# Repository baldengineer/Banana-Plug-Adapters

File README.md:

to USB-A")

These adpaters let you plug common power types into a bench power supply. They require a little bit of caution on your side. For example, don't apply 9 volts to the USB adapter!

Each adapter is two pieces made from a single PCB. The part that holds the banana plugs inserts into the adapter part. Then you solder them together. 

## To use them.
* One pack of [Ponoma 72918 4mm banana plug](https://octopart.com/72918-pomona+electronics-585505?r=sp). 
* Break off the two M3 holes
* Use the tabs to solder them together at 90 degrees
* Optional, add LED with current limiting resistor. 
* Optional, clamping diode.
* Plug into power supply. :)

## Discuss on Discord
Join the [AddOhms/Baldengineer Discord](https://discord.gg/Q3xzyuWqm6) to discuss this project.

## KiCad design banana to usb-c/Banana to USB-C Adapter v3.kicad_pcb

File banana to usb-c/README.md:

# Banana Plug to USB-C (Power Only) Adapter

Based on the `USB4125-GF-A` 6 position surface mount connector.

## Version 3: DFP Fix
Version 2 had placements for pull-down resistors. As the DFP, this board should have pull-up resistors. Turns out, most UFP devices don't care so v2 works fine in most cases.

### Status
2024-OCT-20: V3 has not been tested yet.

## DFP Pull-Up Values
| **DFP Advertisement** | **R Pull-Up to 4.75 - 5.5 V** | **R Pull-Up to 3.3 ±5%** |
| :--- | :---: | :---: |
| **Default USB PWR** | 56 kΩ ± 20% | 36 kΩ ± 20% |
| **1.5 A at 5 V** | 22 kΩ ± 5%  | 12 kΩ ± 5% |
| **3.0 A at 5V** | 10 kΩ ± 5% | 4.7 kΩ ± 5% |

[Values from Infineon KB Article](https://community.infineon.com/t5/Knowledge-Base-Articles/USB-Type-C-connector-Rp-Rd-and-Ra-termination-resistors/ta-p/253544)

## Discuss on Discord
Join the [AddOhms/Baldengineer Discord](https://discord.gg/Q3xzyuWqm6) to discuss this project

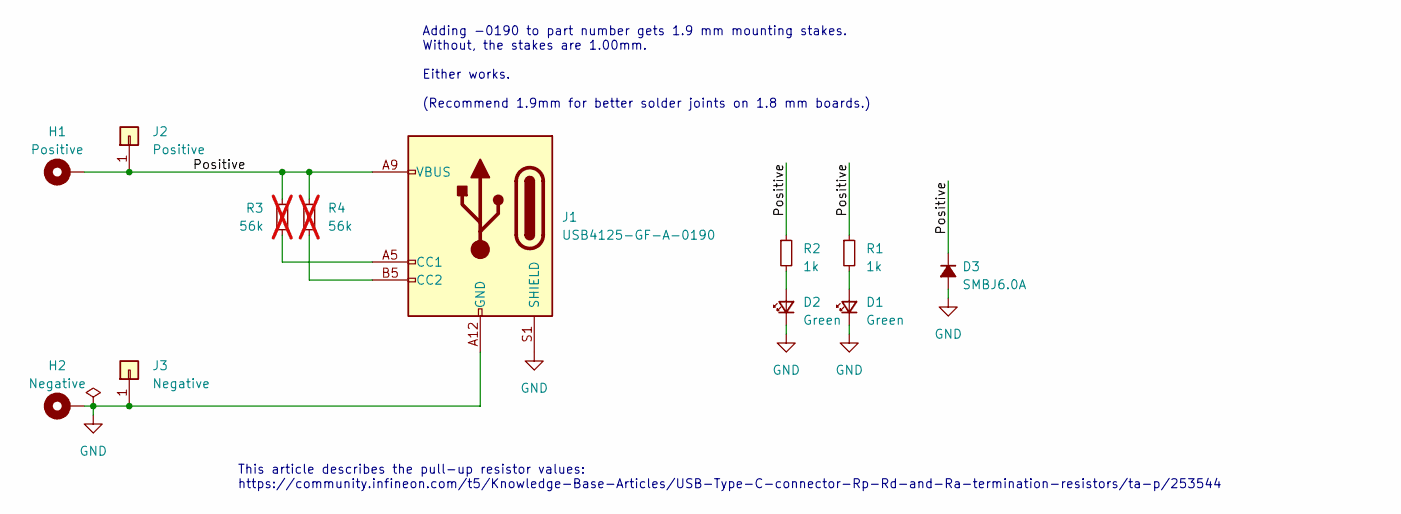
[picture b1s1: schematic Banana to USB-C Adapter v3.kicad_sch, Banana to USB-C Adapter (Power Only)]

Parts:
D1, D2: Green; LED_1206_3216Metric_Pad1.42x1.75mm_HandSolder
D3: SMBJ6.0A; D_SMA-SMB_Universal_Handsoldering
H1: Positive; MountingHole_3.2mm_M3_Pad_Via
H2: Negative; MountingHole_3.2mm_M3_Pad_Via
J1: USB4125-GF-A-0190; USB_C_Receptacle_GCT_USB4125-xx-x_6P_TopMnt_Horizontal
J2: Positive; PinHeader_1x01_P2.54mm_Vertical
J3: Negative; PinHeader_1x01_P2.54mm_Vertical
R1, R2: 1k; R_1206_3216Metric_Pad1.30x1.75mm_HandSolder
R3, R4: 56k; R_1206_3216Metric_Pad1.30x1.75mm_HandSolder; not fitted

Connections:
/Positive: D3.1 (K), H1.1, J1.A9 (VBUS), J1.B9 (VBUS), J2.1, R1.1, R2.1, R3.1, R4.1
GND: D1.1 (K), D2.1 (K), D3.2 (A), H2.1, J1.A12 (GND), J1.B12 (GND), J1.S1 (SHIELD), J3.1
unnamed: D1.2 (A), R1.2
unnamed: D2.2 (A), R2.2
unnamed: J1.A5 (CC1), R3.2
unnamed: J1.B5 (CC2), R4.2

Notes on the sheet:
Adding -0190 to part number gets 1.9 mm mounting stakes. Without, the stakes are 1.00mm. Either works. (Recommend 1.9mm for better solder joints on 1.8 mm boards.)
This article describes the pull-up resistor values: https://community.infineon.com/t5/Knowledge-Base-Articles/USB-Type-C-connector-Rp-Rd-and-Ra-termination-resistors/ta-p/253544

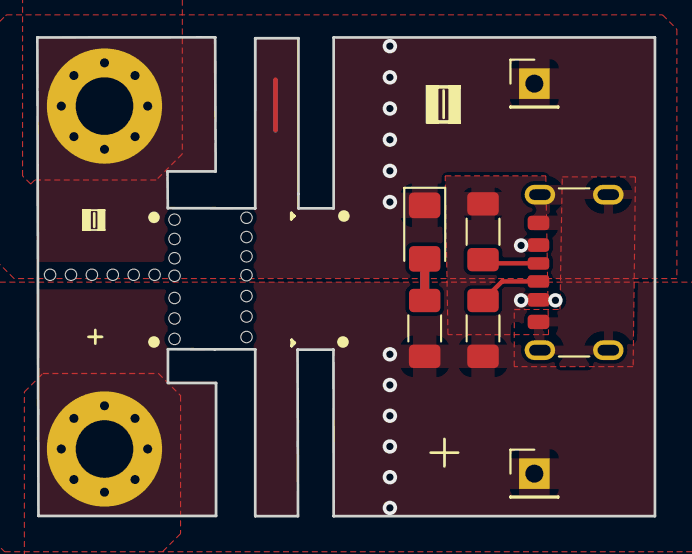
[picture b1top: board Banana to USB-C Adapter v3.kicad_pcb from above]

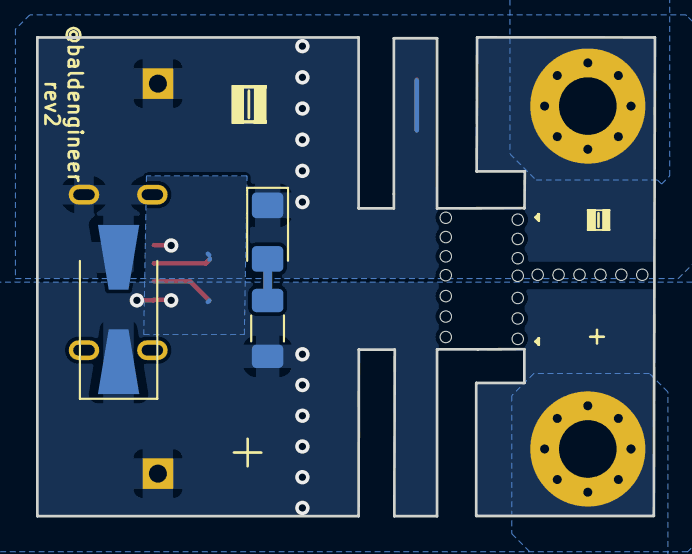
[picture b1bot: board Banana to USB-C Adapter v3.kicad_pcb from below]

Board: 2 copper layers, 34.3 x 26.6 mm, 12 parts (3 on the bottom side), 6 nets.

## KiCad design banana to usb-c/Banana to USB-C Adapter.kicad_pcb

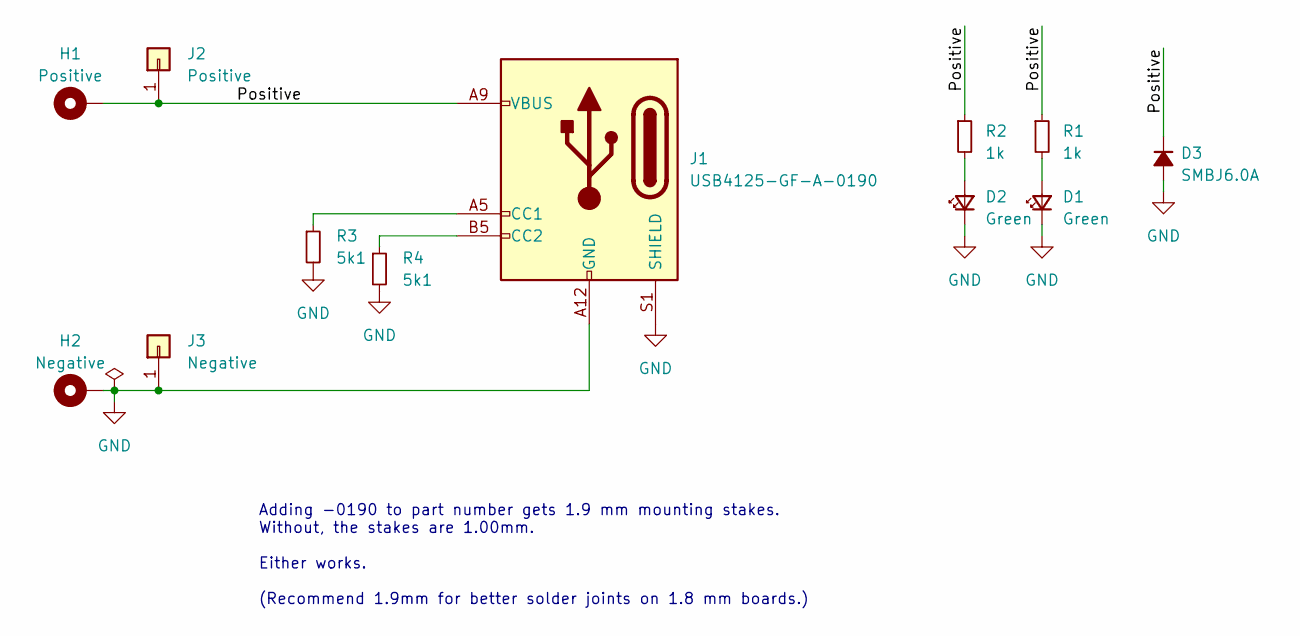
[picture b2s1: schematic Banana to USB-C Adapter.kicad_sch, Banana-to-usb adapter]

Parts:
D1, D2: Green; LED_1206_3216Metric_Pad1.42x1.75mm_HandSolder
D3: SMBJ6.0A; D_SMA-SMB_Universal_Handsoldering
H1: Positive; MountingHole_3.2mm_M3_Pad_Via
H2: Negative; MountingHole_3.2mm_M3_Pad_Via
J1: USB4125-GF-A-0190; USB_C_Receptacle_GCT_USB4125-xx-x_6P_TopMnt_Horizontal
J2: Positive; PinHeader_1x01_P2.54mm_Vertical
J3: Negative; PinHeader_1x01_P2.54mm_Vertical
R1, R2: 1k; R_1206_3216Metric_Pad1.30x1.75mm_HandSolder
R3, R4: 5k1; R_1206_3216Metric_Pad1.30x1.75mm_HandSolder

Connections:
/Positive: D3.1 (K), H1.1, J1.A9 (VBUS), J1.B9 (VBUS), J2.1, R1.1, R2.1
GND: D1.1 (K), D2.1 (K), D3.2 (A), H2.1, J1.A12 (GND), J1.B12 (GND), J1.S1 (SHIELD), J3.1, R3.2, R4.2
unnamed: D1.2 (A), R1.2
unnamed: D2.2 (A), R2.2
unnamed: J1.A5 (CC1), R3.1
unnamed: J1.B5 (CC2), R4.1

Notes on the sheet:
Adding -0190 to part number gets 1.9 mm mounting stakes. Without, the stakes are 1.00mm. Either works. (Recommend 1.9mm for better solder joints on 1.8 mm boards.)

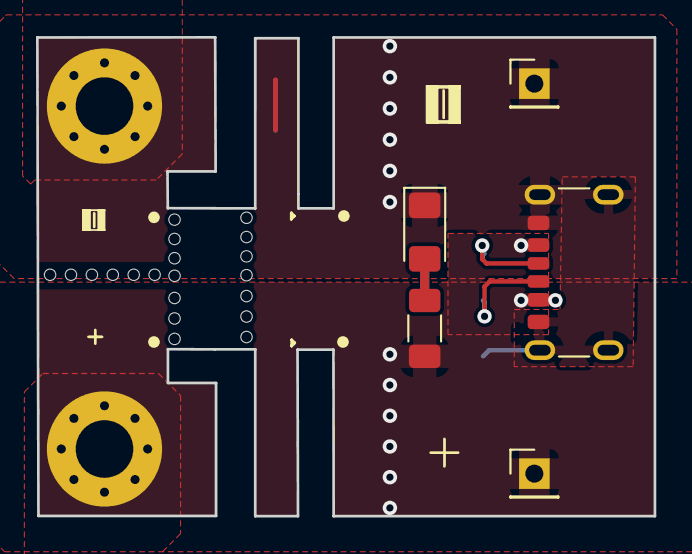
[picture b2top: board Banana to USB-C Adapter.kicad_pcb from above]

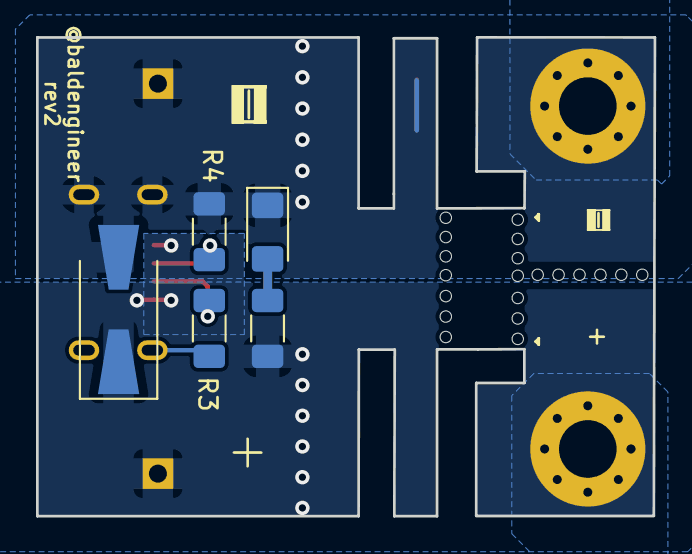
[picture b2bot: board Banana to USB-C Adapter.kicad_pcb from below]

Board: 2 copper layers, 34.3 x 26.6 mm, 12 parts (5 on the bottom side), 6 nets.

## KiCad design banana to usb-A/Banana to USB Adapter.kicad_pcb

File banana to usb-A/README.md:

to USB-A")

## Banana to USB-A Adapter
* Connect USB-A devices to a bench power supply.
* Intended to be used with [Ponoma 72918 banana plug](https://octopart.com/72918-pomona+electronics-585505?r=sp). Break off the two M3 holes, use the tabs to solder them together at 90 degrees, and plug into power supply.
* Rev 1 project link on [OSH Park](https://oshpark.com/shared_projects/gjQOWRep).
* Rev 2 project link on [OSH Park](https://oshpark.com/shared_projects/TIto0uSf).

See root page for instructions on how to use them.

## Discuss on Discord
Join the [AddOhms/Baldengineer Discord](https://discord.gg/Q3xzyuWqm6) to discuss this project

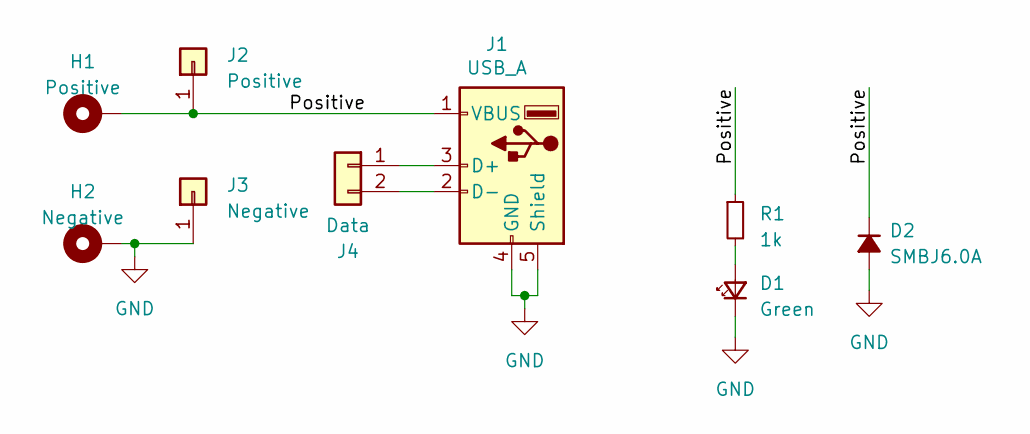
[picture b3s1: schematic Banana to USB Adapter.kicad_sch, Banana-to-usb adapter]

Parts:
D1: Green; LED_1206_3216Metric_Pad1.42x1.75mm_HandSolder
D2: SMBJ6.0A; D_SMA-SMB_Universal_Handsoldering
H1: Positive; MountingHole_3.2mm_M3_Pad_Via
H2: Negative; MountingHole_3.2mm_M3_Pad_Via
J1: USB_A; USB_A_GCT_USB1125; MPN USB1125-GF-B
J2: Positive; PinHeader_1x01_P2.54mm_Vertical
J3: Negative; PinHeader_1x01_P2.54mm_Vertical
J4: Data; PinHeader_1x02_P2.54mm_Vertical
R1: 1k; R_1206_3216Metric_Pad1.30x1.75mm_HandSolder

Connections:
/Positive: D2.1 (K), H1.1, J1.1 (VBUS), J2.1, R1.1
GND: D1.1 (K), D2.2 (A), H2.1, J1.4 (GND), J1.5 (Shield), J3.1
unnamed: D1.2 (A), R1.2
unnamed: J1.3 (D+), J4.1
unnamed: J1.2 (D-), J4.2

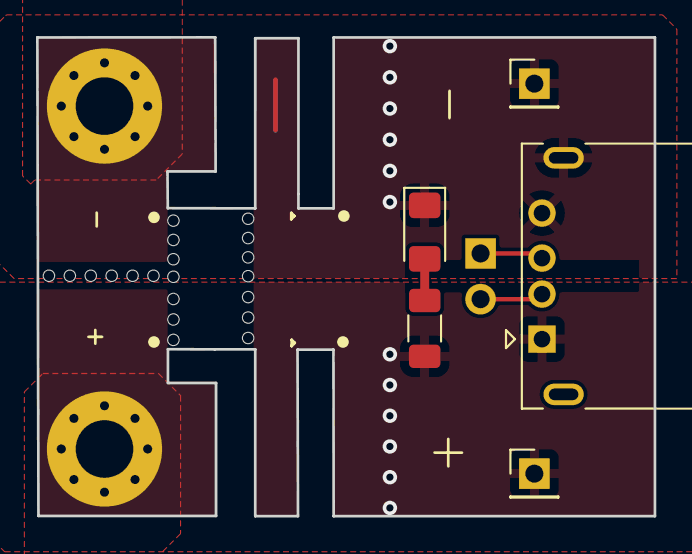
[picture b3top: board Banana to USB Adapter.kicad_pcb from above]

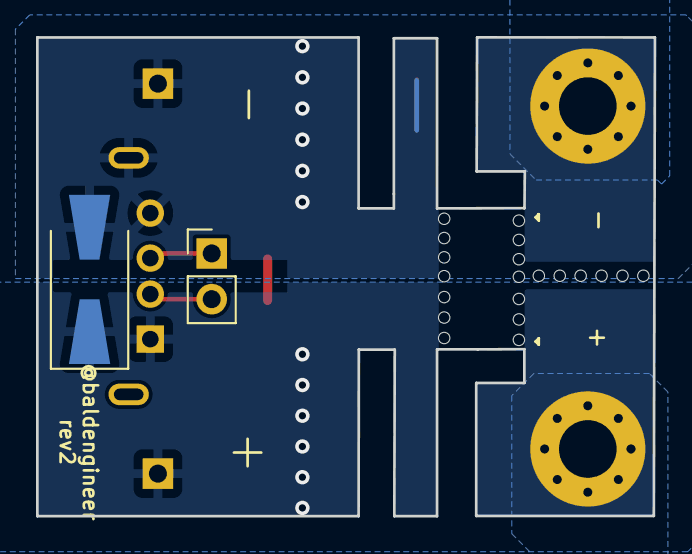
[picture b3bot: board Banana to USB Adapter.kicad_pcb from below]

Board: 2 copper layers, 34.3 x 26.6 mm, 9 parts (2 on the bottom side), 5 nets.

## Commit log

2023-01-20 rev 1 submitted to fab
2023-01-20 added rendered image
2023-03-03 rev2 addresses #2, #3, #5, #6, #7
2023-03-03 rev1 gerbs
2023-03-03 rev2 as submitted to fab
2023-03-03 rev2 gerbs
2023-10-27 rev2 and renaming directories for other adapters
2023-10-27 more name changes
2023-11-21 No design changes to PCB. Removed extra LED reference in schematic, changed TVS diode to D2, and uploaded PCB.
2024-03-14 kicad8 upgrade
2024-04-04 DRC is giving off-grid errors and "GND modified"
2024-04-04 Cleared DRC issues
2024-04-04 Zone Relief DRC error in PCB
2024-04-04 0 DRC before changing zones for positive
2024-04-04 DRC warning about footprints not matching library. going to try and update all.
2024-04-04 passing DRC but lost the breakaway holes for the banana plugs
2024-04-06 put missing drill holes back! (and locked them
2024-04-06 fixed missing drill holes
2024-04-06 barrel jack gerbs (and schematic pdf) ready for fab.
2024-04-06 Updated READMEs, oops.
2024-04-06 initial schematic (pcb is still barrel jack)
2024-04-06 pcb updated with usb-c components, 7 unrouted. yikes.
2024-04-06 usb-c ready for fab
2024-04-06 screw terminal 5.08mm adapter
2024-07-10 fixed typo in readme
2024-07-10 initial jst ph commit
2024-07-10 updated schematic but need to verify pin 1 and 2 connections
2024-07-10 jst ph sm4 adapter rev 2 ready for fab
2024-07-10 added wip to readme
2024-07-10 Changing gerb folder name
2024-07-10 added SPN for JST
2024-10-20 inital usb-c rev3 create
2024-10-20 Updated usbc README with pull-up values
2024-10-20 sch: changed resistors to pull-up and added link to kb article
2024-10-20 updated usbc pcb, generated v3 gerbs
2024-10-20 plotted usbc v3 pdf and updated readme with status
